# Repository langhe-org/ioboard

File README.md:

# ioboard

This circuit board is the interface between a Beaglebone Black and the rest of the greenhouse components.

## Ordering

The part numbers in the BOM and CPL included in the release are generated for JLC PCB. Alternative part numbers will have to be used for other fabrication houses.

## Assembly BOM

The following components are not included in the PCBA and must be purchased and soldered on separately:

- 1x CUI PDQE20-Q24-S5-D
- 2x Mornsun BO505S-1RW3
- 8x Phoenix Contact 1945119
- 4x Phoenix Contact 1945122

## Mating Connectors

Part numbers to mate the the headers:

- 8x Phoenix Contact 1984031
- 4x Phoenix Contact 1984345

## Enclosure

This board is designed to be housed in a Polycase WH-16 enclosure.

https://www.polycase.com/wh-16

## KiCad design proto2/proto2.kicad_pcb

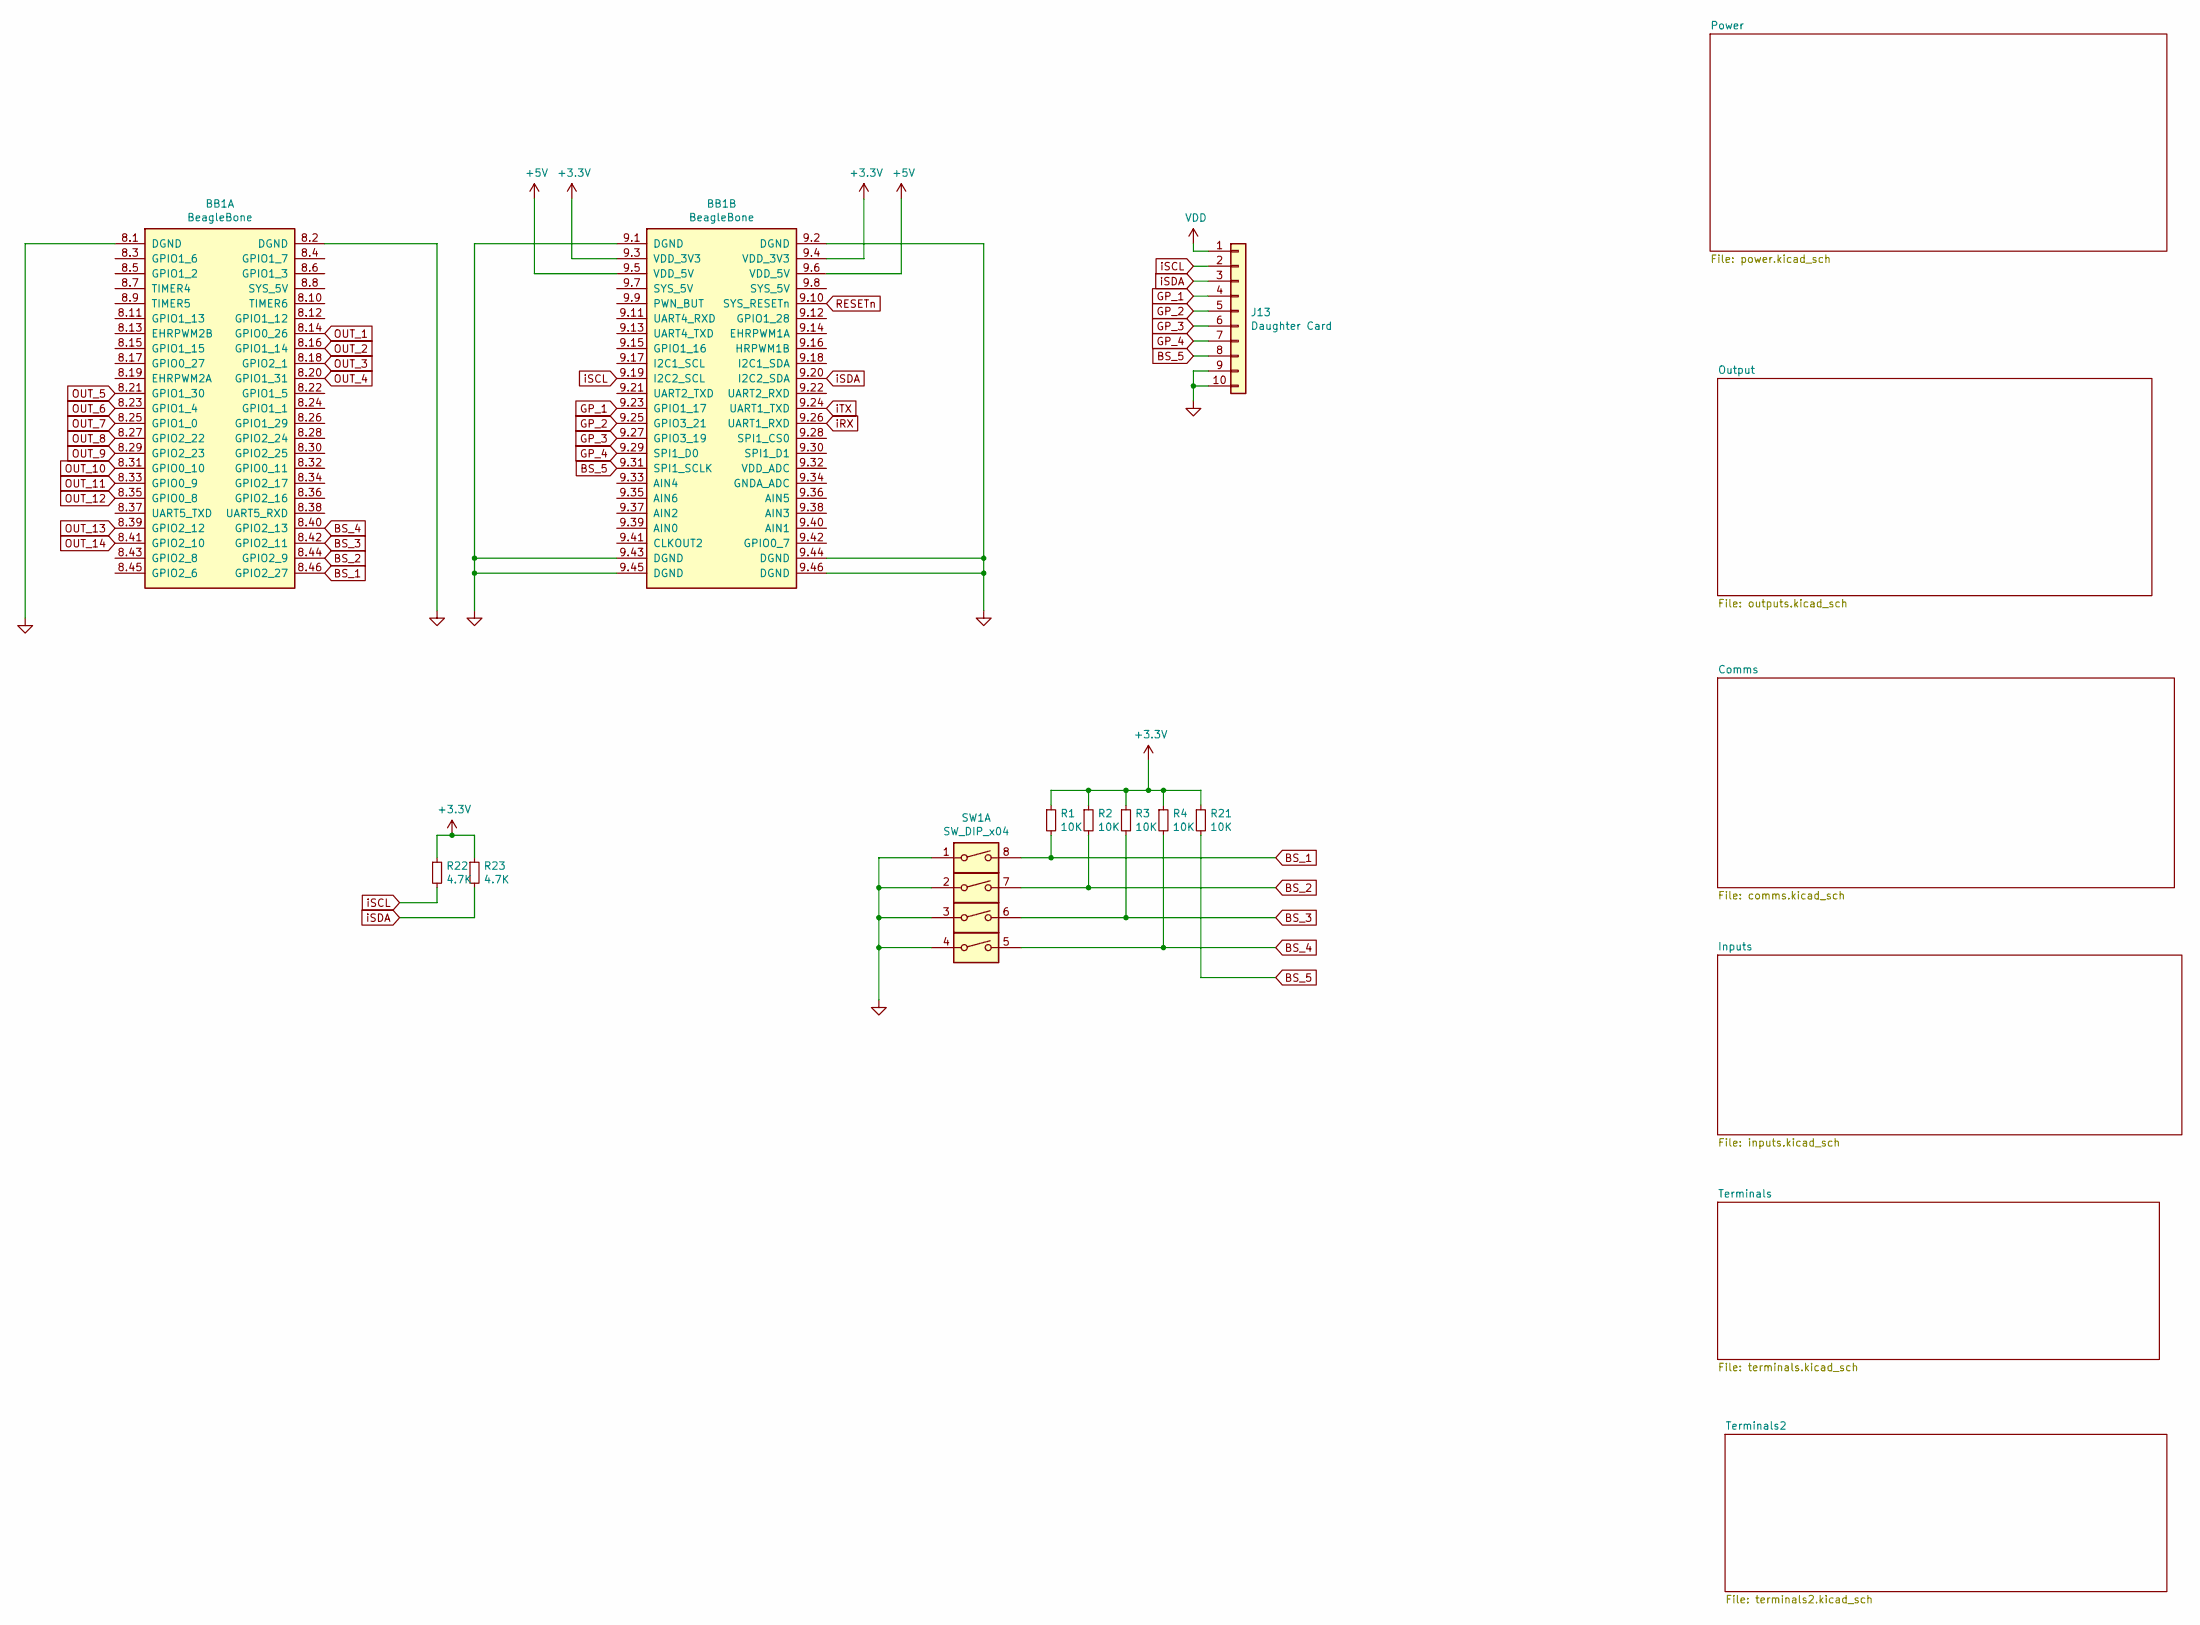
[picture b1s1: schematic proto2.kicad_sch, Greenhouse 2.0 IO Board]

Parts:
BB1: BeagleBone; BeagleBone_UpsideDown
J13: Daughter Card; Proto2_DaughterCard
R1, R2, R3, R4, R21: 10K; R_0805_2012Metric; LCSC C17414
R22, R23: 4.7K; R_0805_2012Metric; LCSC C17673
SW1: SW_DIP_x04; CUI_DS04-254-2-04BK-SMT; Part Number A6S-4101-H; LCSC C306873

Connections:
+5V: BB1.9.5 (VDD_5V), BB1.9.6 (VDD_5V); also elsewhere on the board
BS_1: BB1.8.46 (GPIO2_27), R1.2, SW1.8
BS_2: BB1.8.44 (GPIO2_9), R2.2, SW1.7
BS_3: BB1.8.42 (GPIO2_11), R3.2, SW1.6
BS_4: BB1.8.40 (GPIO2_13), R4.2, SW1.5
BS_5: BB1.9.31 (SPI1_SCLK), J13.8, R21.2
GND-SIG: BB1.8.1 (DGND), BB1.8.2 (DGND), BB1.9.1 (DGND), BB1.9.2 (DGND), BB1.9.43 (DGND), BB1.9.44 (DGND), BB1.9.45 (DGND), BB1.9.46 (DGND), J13.9, J13.10, SW1.1, SW1.2, SW1.3, SW1.4; also elsewhere on the board
GP_1: BB1.9.23 (GPIO1_17), J13.4
GP_2: BB1.9.25 (GPIO3_21), J13.5
GP_3: BB1.9.27 (GPIO3_19), J13.6
GP_4: BB1.9.29 (SPI1_D0), J13.7
OUT_1: BB1.8.14 (GPIO0_26); also elsewhere on the board
OUT_2: BB1.8.16 (GPIO1_14); also elsewhere on the board
OUT_3: BB1.8.18 (GPIO2_1); also elsewhere on the board
OUT_4: BB1.8.20 (GPIO1_31); also elsewhere on the board
OUT_5: BB1.8.21 (GPIO1_30); also elsewhere on the board
OUT_6: BB1.8.23 (GPIO1_4); also elsewhere on the board
OUT_7: BB1.8.25 (GPIO1_0); also elsewhere on the board
OUT_8: BB1.8.27 (GPIO2_22); also elsewhere on the board
OUT_9: BB1.8.29 (GPIO2_23); also elsewhere on the board
OUT_10: BB1.8.31 (GPIO0_10); also elsewhere on the board
OUT_11: BB1.8.33 (GPIO0_9); also elsewhere on the board
OUT_12: BB1.8.35 (GPIO0_8); also elsewhere on the board
OUT_13: BB1.8.39 (GPIO2_12); also elsewhere on the board
OUT_14: BB1.8.41 (GPIO2_10); also elsewhere on the board
RESETn: BB1.9.10 (SYS_RESETn); also elsewhere on the board
VDD: J13.1; also elsewhere on the board
iRX: BB1.9.26 (UART1_RXD); also elsewhere on the board
iSCL: BB1.9.19 (I2C2_SCL), J13.2, R22.2; also elsewhere on the board
iSDA: BB1.9.20 (I2C2_SDA), J13.3, R23.2; also elsewhere on the board
iTX: BB1.9.24 (UART1_TXD); also elsewhere on the board

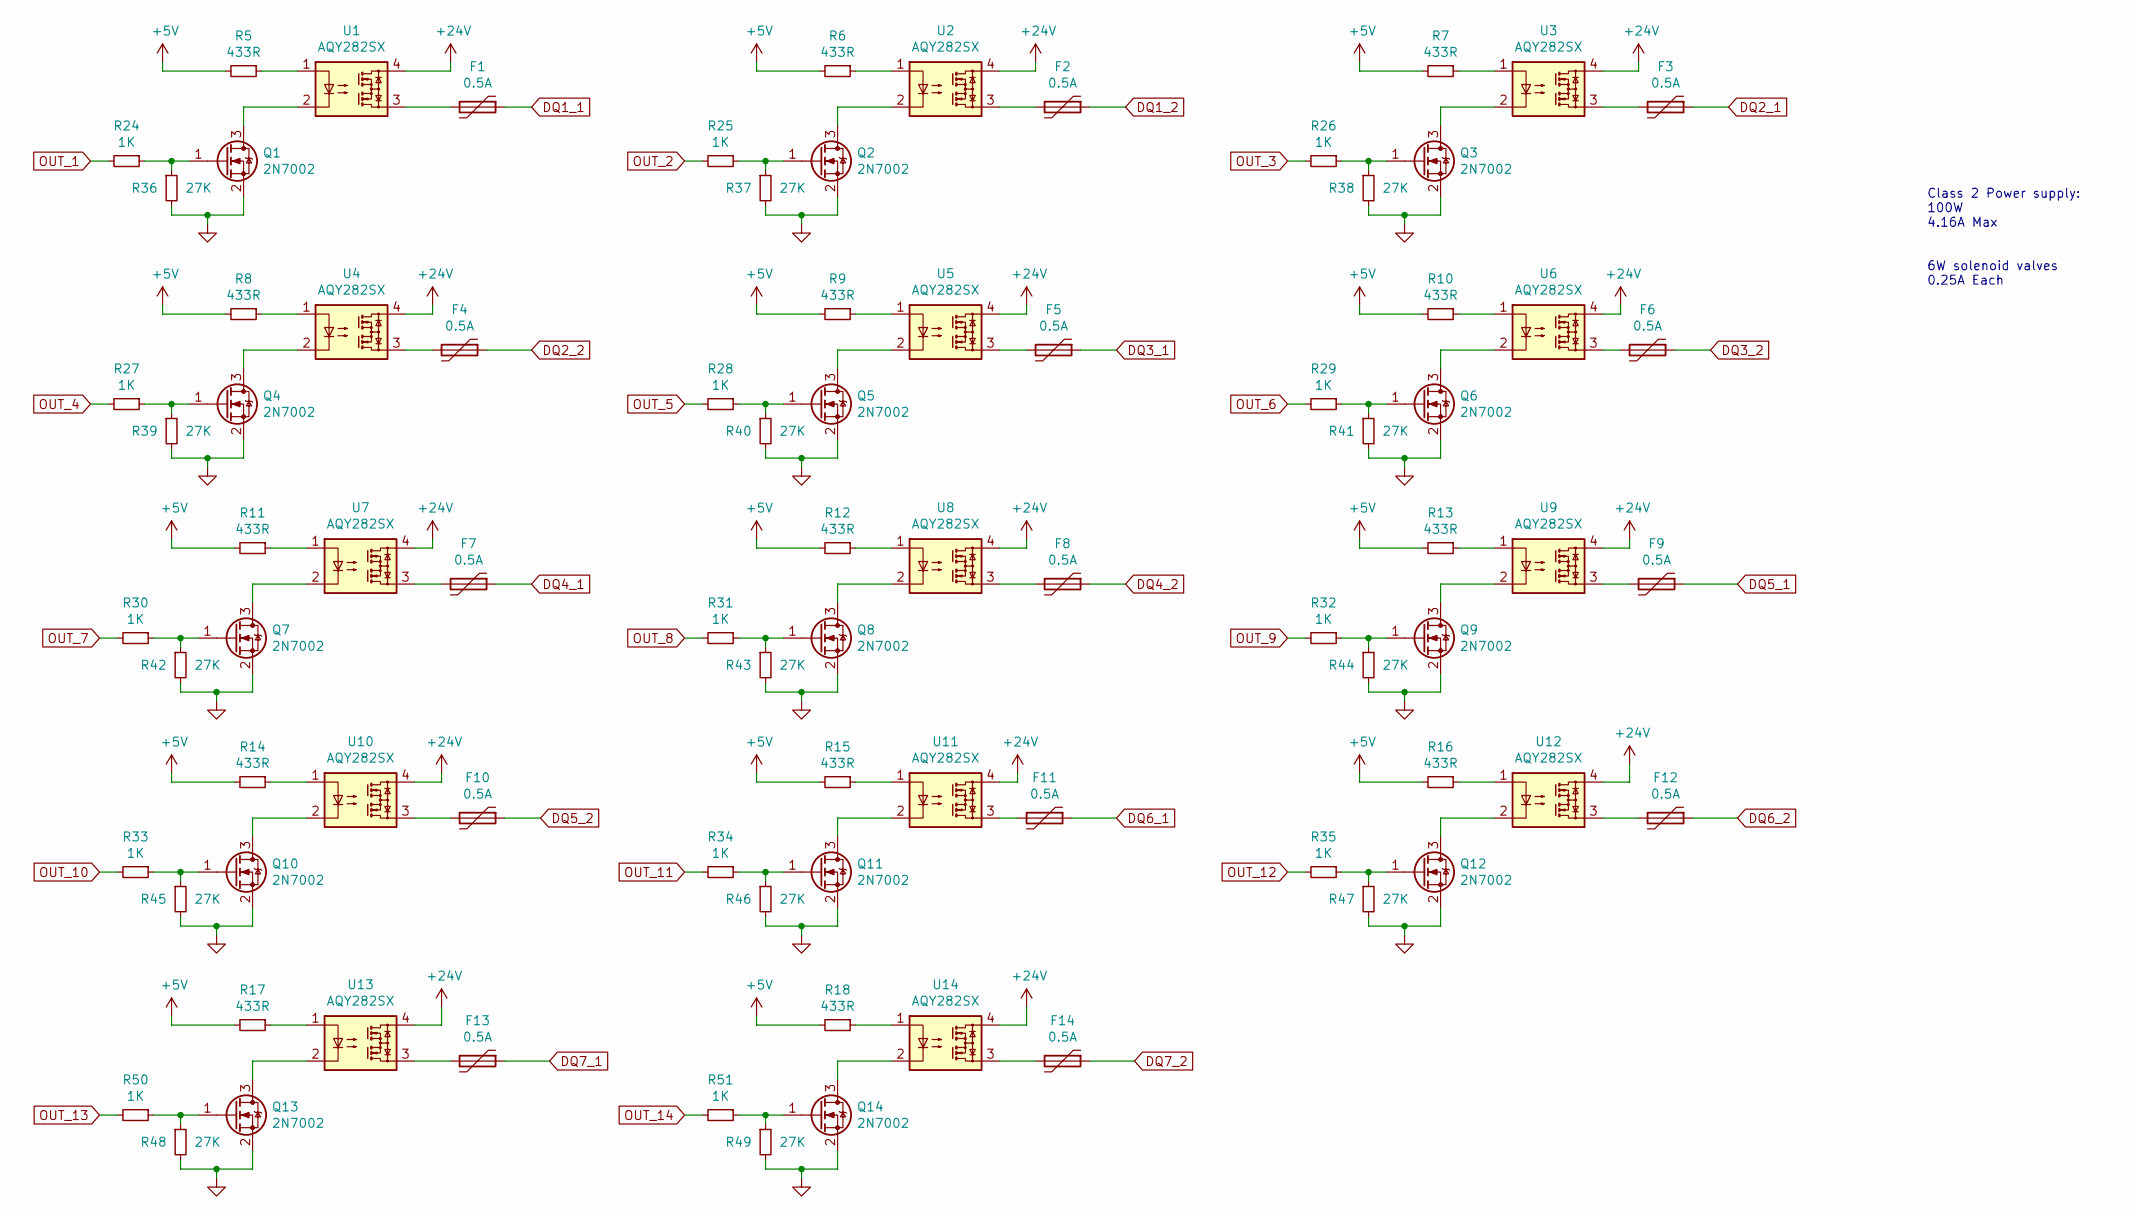
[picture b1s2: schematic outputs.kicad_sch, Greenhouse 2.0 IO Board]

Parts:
F1, F2, F3, F4, F5, F6, F7, F8, F9, F10, F11, F12, F13, F14: 0.5A; R_1206_3216Metric; LCSC C70070
Q1, Q2, Q3, Q4, Q5, Q6, Q7, Q8, Q9, Q10, Q11, Q12, Q13, Q14: 2N7002; SOT-23; LCSC C8545
R5, R6, R7, R8, R9, R10, R11, R12, R13, R14, R15, R16, R17, R18: 433R; R_0805_2012Metric; LCSC C17694
R24, R25, R26, R27, R28, R29, R30, R31, R32, R33, R34, R35, R50, R51: 1K; R_0805_2012Metric; LCSC C17513
R36, R37, R38, R39, R40, R41, R42, R43, R44, R45, R46, R47, R48, R49: 27K; R_0805_2012Metric; LCSC C17593
U1, U2, U3, U4, U5, U6, U7, U8, U9, U10, U11, U12, U13, U14: AQY282SX; SO-4_4.4x4.3mm_P2.54mm; LCSC C250827

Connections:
+5V: R5.2, R6.2, R7.2, R8.2, R9.2, R10.2, R11.2, R12.2, R13.2, R14.2, R15.2, R16.2, R17.2, R18.2; also elsewhere on the board
+24V: U1.4, U2.4, U3.4, U4.4, U5.4, U6.4, U7.4, U8.4, U9.4, U10.4, U11.4, U12.4, U13.4, U14.4; also elsewhere on the board
DQ1_1: F1.1; also elsewhere on the board
DQ1_2: F2.1; also elsewhere on the board
DQ2_1: F3.1; also elsewhere on the board
DQ2_2: F4.1; also elsewhere on the board
DQ3_1: F5.1; also elsewhere on the board
DQ3_2: F6.1; also elsewhere on the board
DQ4_1: F7.1; also elsewhere on the board
DQ4_2: F8.1; also elsewhere on the board
DQ5_1: F9.1; also elsewhere on the board
DQ5_2: F10.1; also elsewhere on the board
DQ6_1: F11.1; also elsewhere on the board
DQ6_2: F12.1; also elsewhere on the board
DQ7_1: F13.1; also elsewhere on the board
DQ7_2: F14.1; also elsewhere on the board
GND-SIG: Q1.2 (S), Q2.2 (S), Q3.2 (S), Q4.2 (S), Q5.2 (S), Q6.2 (S), Q7.2 (S), Q8.2 (S), Q9.2 (S), Q10.2 (S), Q11.2 (S), Q12.2 (S), Q13.2 (S), Q14.2 (S), R36.2, R37.2, R38.2, R39.2, R40.2, R41.2, R42.2, R43.2, R44.2, R45.2, R46.2, R47.2, R48.2, R49.2; also elsewhere on the board
unnamed: F1.2, U1.3
unnamed: F2.2, U2.3
unnamed: F3.2, U3.3
unnamed: F4.2, U4.3
unnamed: F5.2, U5.3
unnamed: F6.2, U6.3
unnamed: F7.2, U7.3
unnamed: F8.2, U8.3
unnamed: F9.2, U9.3
unnamed: F10.2, U10.3
unnamed: F11.2, U11.3
unnamed: F12.2, U12.3
unnamed: F13.2, U13.3
unnamed: F14.2, U14.3
unnamed: Q1.1 (G), R24.1, R36.1
unnamed: Q1.3 (D), U1.2
unnamed: Q2.1 (G), R25.1, R37.1
unnamed: Q2.3 (D), U2.2
unnamed: Q3.1 (G), R26.1, R38.1
unnamed: Q3.3 (D), U3.2
unnamed: Q4.1 (G), R27.1, R39.1
unnamed: Q4.3 (D), U4.2
unnamed: Q5.1 (G), R28.1, R40.1
unnamed: Q5.3 (D), U5.2
unnamed: Q6.1 (G), R29.1, R41.1
unnamed: Q6.3 (D), U6.2
unnamed: Q7.1 (G), R30.1, R42.1
unnamed: Q7.3 (D), U7.2
unnamed: Q8.1 (G), R31.1, R43.1
unnamed: Q8.3 (D), U8.2
unnamed: Q9.1 (G), R32.1, R44.1
unnamed: Q9.3 (D), U9.2
unnamed: Q10.1 (G), R33.1, R45.1
unnamed: Q10.3 (D), U10.2
unnamed: Q11.1 (G), R34.1, R46.1
unnamed: Q11.3 (D), U11.2
unnamed: Q12.1 (G), R35.1, R47.1
unnamed: Q12.3 (D), U12.2
unnamed: Q13.1 (G), R48.1, R50.1
unnamed: Q13.3 (D), U13.2
unnamed: Q14.1 (G), R49.1, R51.1
unnamed: Q14.3 (D), U14.2
unnamed: R5.1, U1.1
unnamed: R6.1, U2.1
unnamed: R7.1, U3.1
unnamed: R8.1, U4.1
unnamed: R9.1, U5.1
unnamed: R10.1, U6.1
unnamed: R11.1, U7.1
unnamed: R12.1, U8.1
unnamed: R13.1, U9.1
unnamed: R14.1, U10.1
unnamed: R15.1, U11.1
unnamed: R16.1, U12.1
unnamed: R17.1, U13.1
unnamed: R18.1, U14.1
OUT_1: R24.2; also elsewhere on the board
OUT_2: R25.2; also elsewhere on the board
OUT_3: R26.2; also elsewhere on the board
OUT_4: R27.2; also elsewhere on the board
OUT_5: R28.2; also elsewhere on the board
OUT_6: R29.2; also elsewhere on the board
OUT_7: R30.2; also elsewhere on the board
OUT_8: R31.2; also elsewhere on the board
OUT_9: R32.2; also elsewhere on the board
OUT_10: R33.2; also elsewhere on the board
OUT_11: R34.2; also elsewhere on the board
OUT_12: R35.2; also elsewhere on the board
OUT_13: R50.2; also elsewhere on the board
OUT_14: R51.2; also elsewhere on the board

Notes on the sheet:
Class 2 Power supply: 100W 4.16A Max 6W solenoid valves 0.25A Each

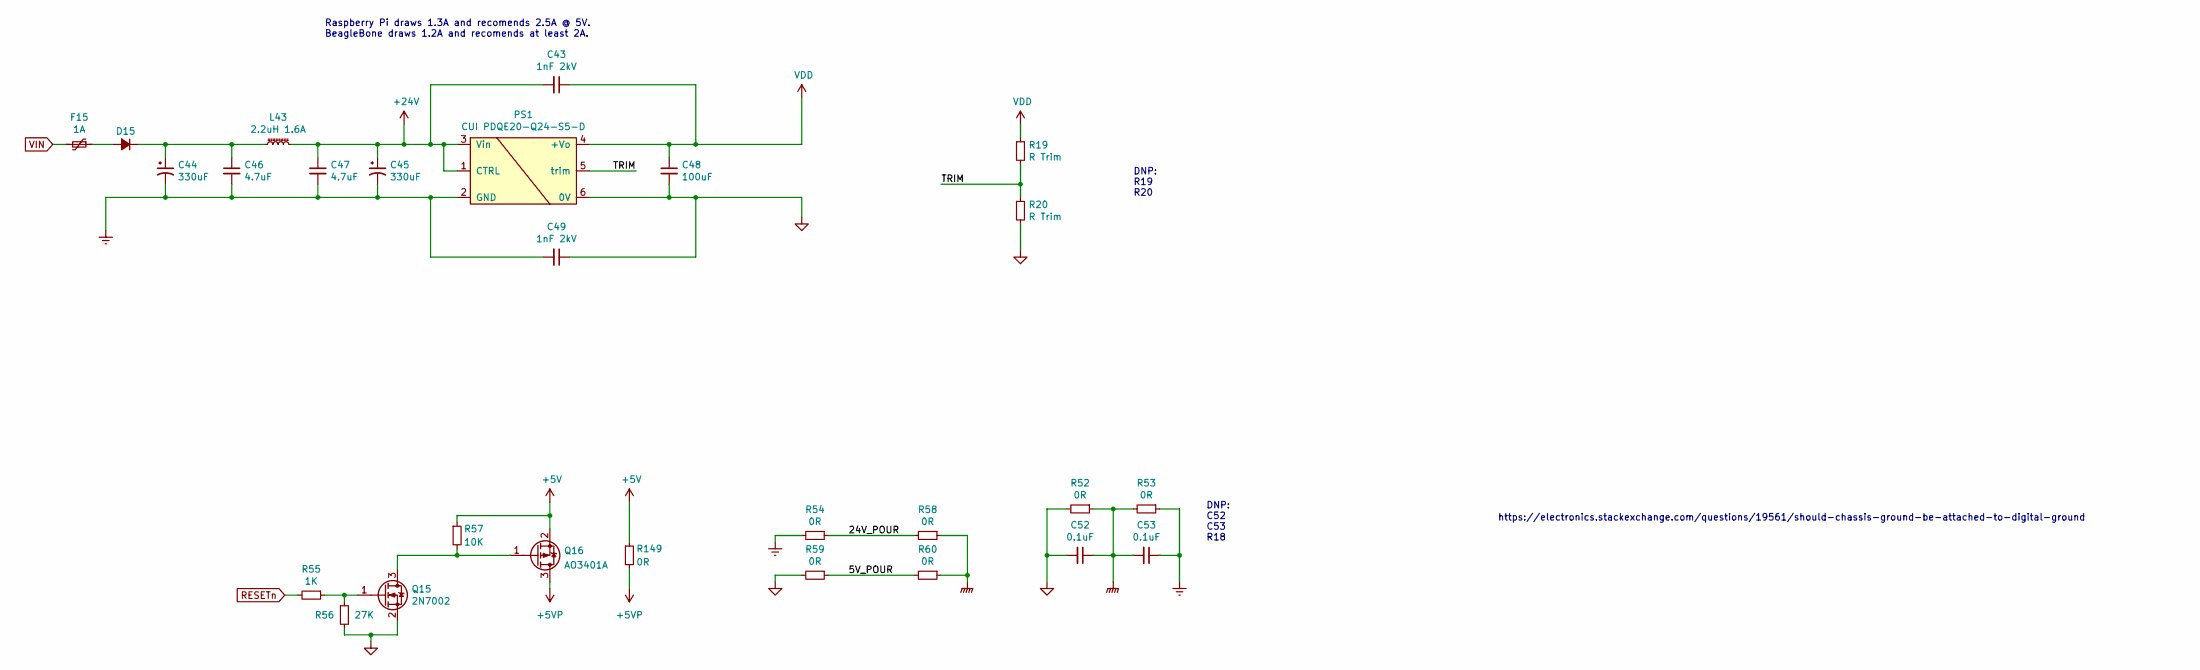
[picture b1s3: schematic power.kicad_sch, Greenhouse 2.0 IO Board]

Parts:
C43, C49: 1nF 2kV; C_1206_3216Metric; LCSC C9196
C44, C45: 330uF; CP_Elec_13x12.5; LCSC C94443
C46, C47: 4.7uF; C_1206_3216Metric; LCSC C29823
C48: 100uF; C_1206_3216Metric; LCSC C312983
C52, C53: 0.1uF; C_0805_2012Metric
D15: D_Small_ALT; D_SOD-123F; Part Number SM4007PL; LCSC C64898
F15: 1A; R_1206_3216Metric; LCSC C70077
L43: 2.2uH 1.6A; Murata_LQH32PN2R2NN0L; Part Number LQH32PN2R2NN0L; LCSC C86074
PS1: CUI PDQE20-Q24-S5-D; CUI_PDQE20; Part Number PDQE20-Q24-S5-D
Q15: 2N7002; SOT-23; LCSC C8545
Q16: AO3401A; SOT-23; Part Number A03401A; LCSC C15127
R19, R20: R Trim; C_0805_2012Metric
R52, R53, R54, R58, R59, R60, R149: 0R; R_0805_2012Metric; LCSC C17477
R55: 1K; R_0805_2012Metric; LCSC C17513
R56: 27K; R_0805_2012Metric; LCSC C17593
R57: 10K; R_0805_2012Metric; LCSC C17414

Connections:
+5V: Q16.2 (S), R57.1, R149.1; also elsewhere on the board
+5VP: Q16.3 (D), R149.2; also elsewhere on the board
+24V: C43.2, C45.1, C47.1, L43.2, PS1.1 (CTRL), PS1.3 (Vin); also elsewhere on the board
/Power/5V_POUR: R59.1, R60.2
/Power/24V_POUR: R54.1, R58.2
/Power/TRIM: PS1.5 (trim), R19.2, R20.1
GND-PE: C52.1, C53.2, R52.1, R53.2, R58.1, R60.1; also elsewhere on the board
GND-PWR: C44.2, C45.2, C46.2, C47.2, C49.2, C53.1, PS1.2 (GND), R53.1, R54.2; also elsewhere on the board
GND-SIG: C48.2, C49.1, C52.2, PS1.6 (0V), Q15.2 (S), R20.2, R52.2, R56.2, R59.2; also elsewhere on the board
unnamed: C44.1, C46.1, D15.1 (K), L43.1
unnamed: D15.2 (A), F15.1
unnamed: Q15.1 (G), R55.1, R56.1
unnamed: Q15.3 (D), Q16.1 (G), R57.2
RESETn: R55.2; also elsewhere on the board
VDD: C43.1, C48.1, PS1.4 (+Vo), R19.1; also elsewhere on the board
VIN: F15.2; also elsewhere on the board

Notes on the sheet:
https://electronics.stackexchange.com/questions/19561/should-chassis-ground-be-attached-to-digital-ground
DNP: R19 R20
Raspberry Pi draws 1.3A and recomends 2.5A @ 5V. BeagleBone draws 1.2A and recomends at least 2A.
DNP: C52 C53 R18

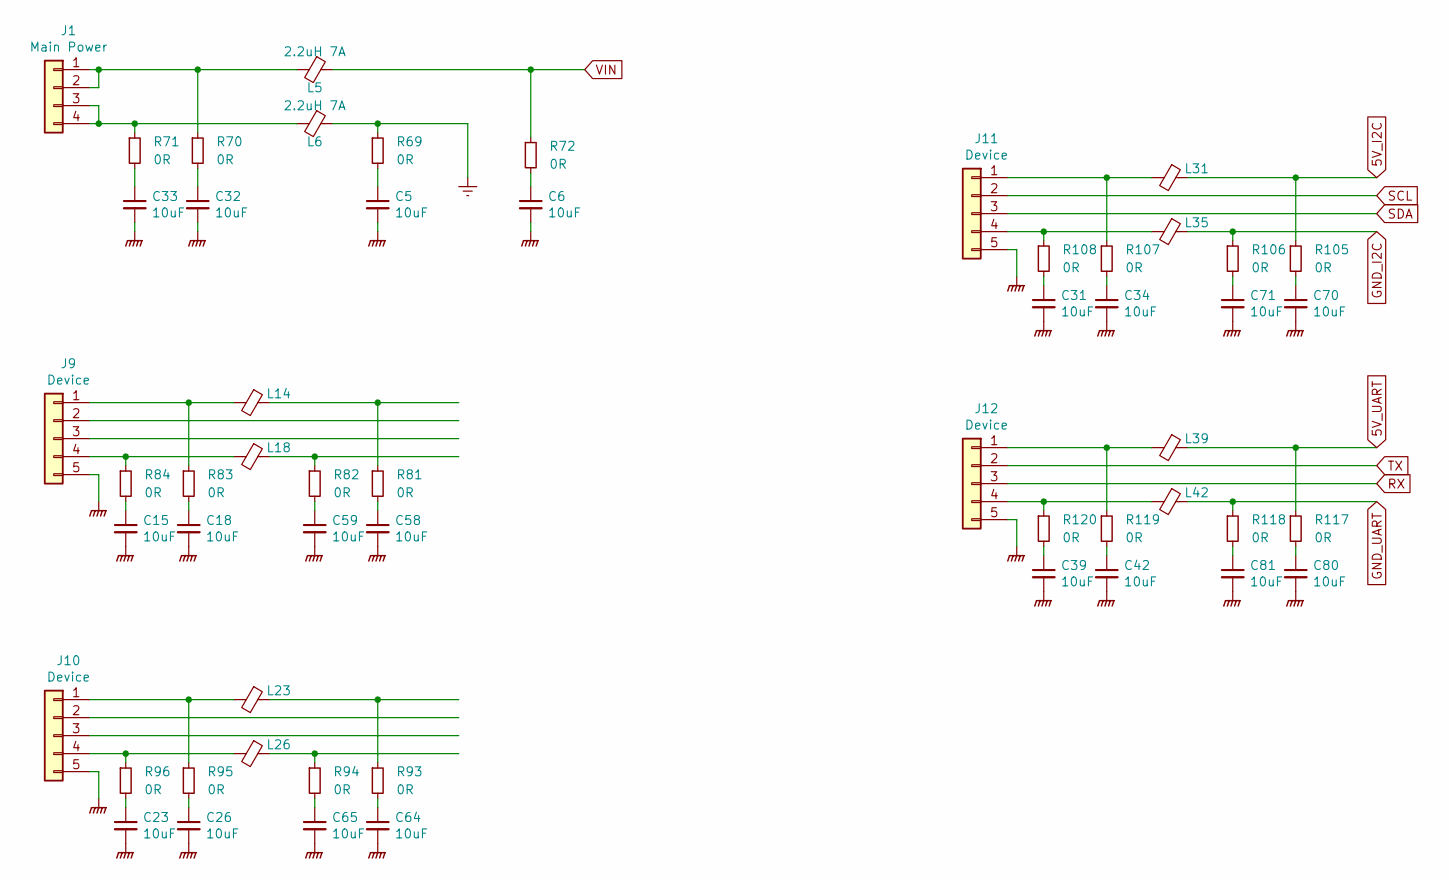
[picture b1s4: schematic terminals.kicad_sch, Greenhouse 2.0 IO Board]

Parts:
C5, C6, C15, C18, C23, C26, C31, C32, C33, C34, C39, C42, C58, C59, C64, C65, C70, C71, C80, C81: 10uF; C_0805_2012Metric; LCSC C440198
J1: Main Power; Phoenix_Contact_PST_4
J9, J10, J11, J12: Device; Phoenix_Contact_PST_5
L5, L6: 2.2uH 7A; Coilmax_MS0630-2R2M; Part Number MS0630-2R2M; LCSC C380175
L14, L18, L23, L26, L31, L35, L39, L42: 10uH 500mA; L_0805_2012Metric; Part Number MGFL2012F100MT; LCSC C281113
R69, R70, R71, R72, R81, R82, R83, R84, R93, R94, R95, R96, R105, R106, R107, R108, R117, R118, R119, R120: 0R; R_0805_2012Metric; LCSC C17477

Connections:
5V_I2C: L31.1, R105.1; also elsewhere on the board
5V_UART: L39.1, R117.1; also elsewhere on the board
GND-PE: C5.2, C6.2, C15.2, C18.2, C23.2, C26.2, C31.2, C32.2, C33.2, C34.2, C39.2, C42.2, C58.2, C59.2, C64.2, C65.2, C70.2, C71.2, C80.2, C81.2, J9.5, J10.5, J11.5, J12.5; also elsewhere on the board
GND-PWR: L6.1, R69.1; also elsewhere on the board
GND_I2C: L35.1, R106.1; also elsewhere on the board
GND_UART: L42.1, R118.1; also elsewhere on the board
unnamed: C5.1, R69.2
unnamed: C6.1, R72.2
unnamed: C15.1, R84.2
unnamed: C18.1, R83.2
unnamed: C23.1, R96.2
unnamed: C26.1, R95.2
unnamed: C31.1, R108.2
unnamed: C32.1, R70.2
unnamed: C33.1, R71.2
unnamed: C34.1, R107.2
unnamed: C39.1, R120.2
unnamed: C42.1, R119.2
unnamed: C58.1, R81.2
unnamed: C59.1, R82.2
unnamed: C64.1, R93.2
unnamed: C65.1, R94.2
unnamed: C70.1, R105.2
unnamed: C71.1, R106.2
unnamed: C80.1, R117.2
unnamed: C81.1, R118.2
unnamed: J1.1, J1.2, L5.2, R70.1
unnamed: J1.3, J1.4, L6.2, R71.1
unnamed: J9.1, L14.2, R83.1
unnamed: J9.4, L18.2, R84.1
unnamed: J10.1, L23.2, R95.1
unnamed: J10.4, L26.2, R96.1
unnamed: J11.1, L31.2, R107.1
unnamed: J11.4, L35.2, R108.1
unnamed: J12.1, L39.2, R119.1
unnamed: J12.4, L42.2, R120.1
unnamed: L14.1, R81.1
unnamed: L18.1, R82.1
unnamed: L23.1, R93.1
unnamed: L26.1, R94.1
RX: J12.3; also elsewhere on the board
SCL: J11.2; also elsewhere on the board
SDA: J11.3; also elsewhere on the board
TX: J12.2; also elsewhere on the board
VIN: L5.1, R72.1; also elsewhere on the board

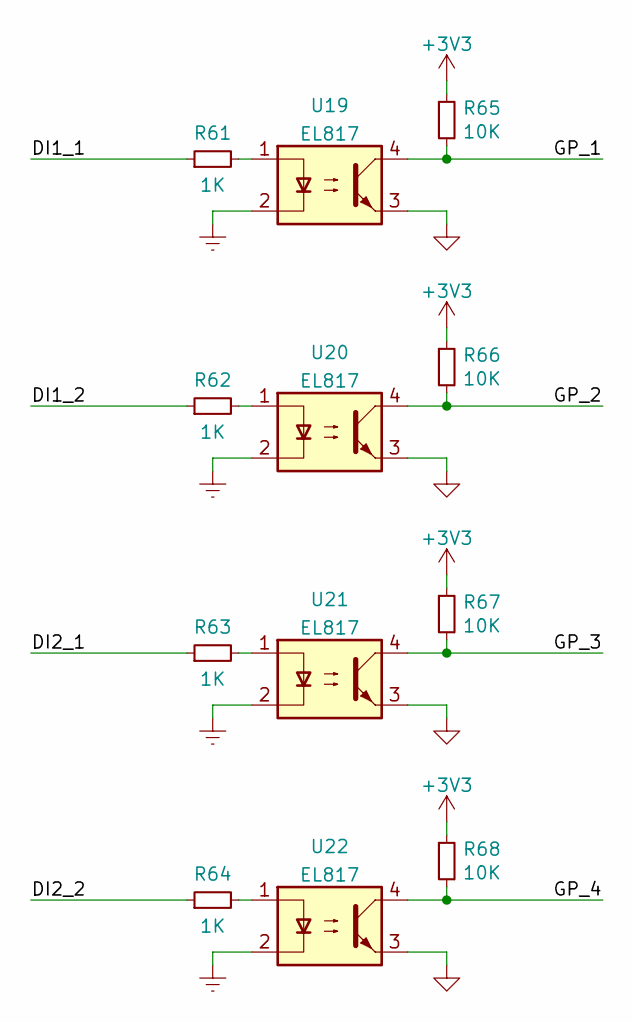
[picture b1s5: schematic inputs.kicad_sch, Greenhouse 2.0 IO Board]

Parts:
R61, R62, R63, R64: 1K; R_0805_2012Metric; LCSC C17513
R65, R66, R67, R68: 10K; R_0805_2012Metric; LCSC C17414
U19, U20, U21, U22: EL817; SO-4_7.6x3.6mm_P2.54mm; Part Number EL817; LCSC C106900

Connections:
/Inputs/DI1_1: R61.1
/Inputs/DI1_2: R62.1
/Inputs/DI2_1: R63.1
/Inputs/DI2_2: R64.1
/Inputs/GP_1: R65.2, U19.4
/Inputs/GP_2: R66.2, U20.4
/Inputs/GP_3: R67.2, U21.4
/Inputs/GP_4: R68.2, U22.4
GND-PWR: U19.2, U20.2, U21.2, U22.2; also elsewhere on the board
GND-SIG: U19.3, U20.3, U21.3, U22.3; also elsewhere on the board
unnamed: R61.2, U19.1
unnamed: R62.2, U20.1
unnamed: R63.2, U21.1
unnamed: R64.2, U22.1

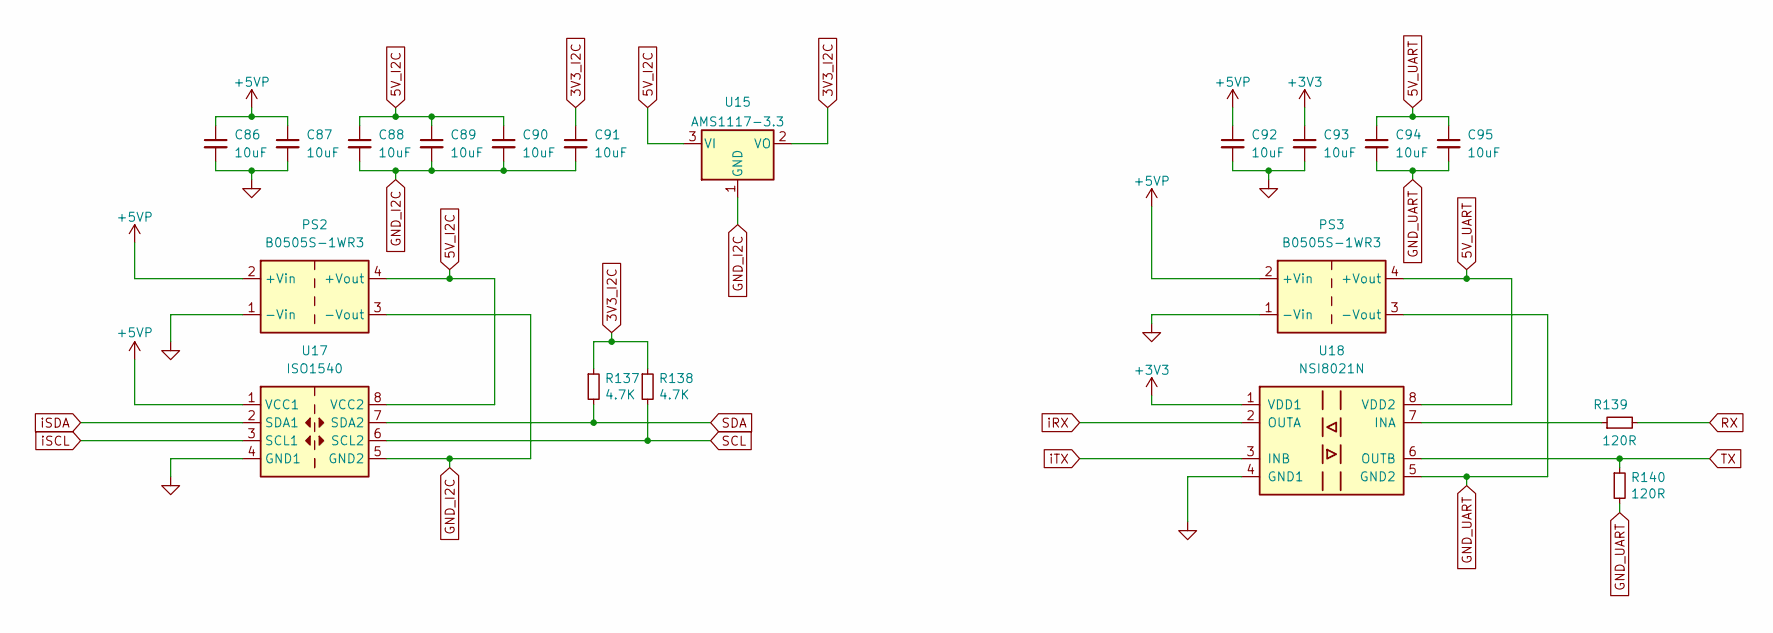
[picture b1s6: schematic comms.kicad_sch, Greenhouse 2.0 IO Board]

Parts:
C86, C87, C88, C89, C90, C91, C92, C93, C94, C95: 10uF; C_0805_2012Metric; LCSC C440198
PS2, PS3: B0505S-1WR3; Converter_DCDC_Murata_MEE1SxxxxSC_THT; LCSC C131038
R137, R138: 4.7K; R_0805_2012Metric; LCSC C17673
R139, R140: 120R; R_0805_2012Metric; LCSC C17437
U15: AMS1117-3.3; SOT-223-3_TabPin2; Part Number AMS1117-3.3; LCSC C6186
U17: ISO1540; SOIC-8_3.9x4.9mm_P1.27mm; Part Number ISO1540DR; LCSC C179739
U18: NSI8021N; SOIC-8_3.9x4.9mm_P1.27mm; Part Number NSI8021N-DSPR; LCSC C917451

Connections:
3V3_I2C: C91.1, R137.1, R138.1, U15.2 (VO)
5V_I2C: C88.1, C89.1, C90.1, PS2.4 (+Vout), U15.3 (VI), U17.8 (VCC2); also elsewhere on the board
5V_UART: C94.1, C95.1, PS3.4 (+Vout), U18.8 (VDD2); also elsewhere on the board
+5VP: C86.1, C87.1, C92.1, PS2.2 (+Vin), PS3.2 (+Vin), U17.1 (VCC1); also elsewhere on the board
GND-SIG: C86.2, C87.2, C92.2, C93.2, PS2.1 (-Vin), PS3.1 (-Vin), U17.4 (GND1), U18.4 (GND1); also elsewhere on the board
GND_I2C: C88.2, C89.2, C90.2, C91.2, PS2.3 (-Vout), U15.1 (GND), U17.5 (GND2); also elsewhere on the board
GND_UART: C94.2, C95.2, PS3.3 (-Vout), R140.2, U18.5 (GND2); also elsewhere on the board
unnamed: R139.1, U18.7 (INA)
RX: R139.2; also elsewhere on the board
SCL: R138.2, U17.6 (SCL2); also elsewhere on the board
SDA: R137.2, U17.7 (SDA2); also elsewhere on the board
TX: R140.1, U18.6 (OUTB); also elsewhere on the board
iRX: U18.2 (OUTA); also elsewhere on the board
iSCL: U17.3 (SCL1); also elsewhere on the board
iSDA: U17.2 (SDA1); also elsewhere on the board
iTX: U18.3 (INB); also elsewhere on the board

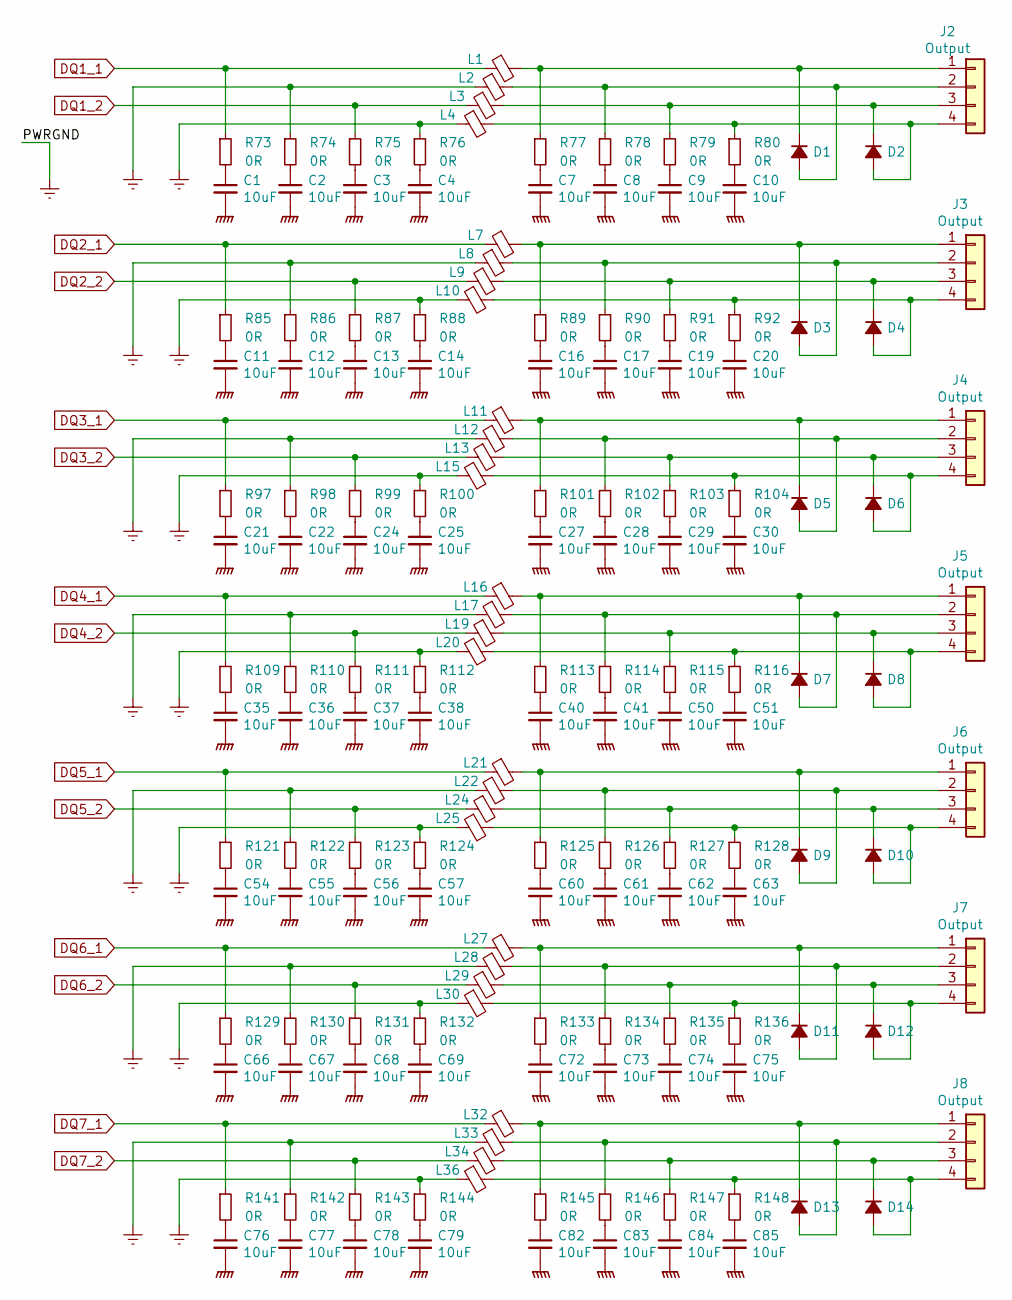
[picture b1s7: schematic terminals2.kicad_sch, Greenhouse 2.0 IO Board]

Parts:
C1, C2, C3, C4, C7, C8, C9, C10, C11, C12, C13, C14, C16, C17, C19, C20, C21, C22, C24, C25, C27, C28, C29, C30, C35, C36, C37, C38, C40, C41, C50, C51, C54, C55, C56, C57, C60, C61, C62, C63, C66, C67, C68, C69, C72, C73, C74, C75, C76, C77, C78, C79, C82, C83, C84, C85: 10uF; C_0805_2012Metric; LCSC C440198
D1, D2, D3, D4, D5, D6, D7, D8, D9, D10, D11, D12, D13, D14: D_Small_ALT; D_SOD-123F; Part Number SM4007PL; LCSC C64898
J2, J3, J4, J5, J6, J7, J8: Output; Phoenix_Contact_PST_4
L1, L2, L3, L4, L7, L8, L9, L10, L11, L12, L13, L15, L16, L17, L19, L20, L21, L22, L24, L25, L27, L28, L29, L30, L32, L33, L34, L36: 10uH 500mA; L_0805_2012Metric; Part Number MGFL2012F100MT; LCSC C281113
R73, R74, R75, R76, R77, R78, R79, R80, R85, R86, R87, R88, R89, R90, R91, R92, R97, R98, R99, R100, R101, R102, R103, R104, R109, R110, R111, R112, R113, R114, R115, R116, R121, R122, R123, R124, R125, R126, R127, R128, R129, R130, R131, R132, R133, R134, R135, R136, R141, R142, R143, R144, R145, R146, R147, R148: 0R; R_0805_2012Metric; LCSC C17477

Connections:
DQ1_1: L1.1, R73.1; also elsewhere on the board
DQ1_2: L3.1, R75.1; also elsewhere on the board
DQ2_1: L7.1, R85.1; also elsewhere on the board
DQ2_2: L9.1, R87.1; also elsewhere on the board
DQ3_1: L11.1, R97.1; also elsewhere on the board
DQ3_2: L13.1, R99.1; also elsewhere on the board
DQ4_1: L16.1, R109.1; also elsewhere on the board
DQ4_2: L19.1, R111.1; also elsewhere on the board
DQ5_1: L21.1, R121.1; also elsewhere on the board
DQ5_2: L24.1, R123.1; also elsewhere on the board
DQ6_1: L27.1, R129.1; also elsewhere on the board
DQ6_2: L29.1, R131.1; also elsewhere on the board
DQ7_1: L32.1, R141.1; also elsewhere on the board
DQ7_2: L34.1, R143.1; also elsewhere on the board
GND-PE: C1.2, C2.2, C3.2, C4.2, C7.2, C8.2, C9.2, C10.2, C11.2, C12.2, C13.2, C14.2, C16.2, C17.2, C19.2, C20.2, C21.2, C22.2, C24.2, C25.2, C27.2, C28.2, C29.2, C30.2, C35.2, C36.2, C37.2, C38.2, C40.2, C41.2, C50.2, C51.2, C54.2, C55.2, C56.2, C57.2, C60.2, C61.2, C62.2, C63.2, C66.2, C67.2, C68.2, C69.2, C72.2, C73.2, C74.2, C75.2, C76.2, C77.2, C78.2, C79.2, C82.2, C83.2, C84.2, C85.2; also elsewhere on the board
GND-PWR: L2.1, L4.1, L8.1, L10.1, L12.1, L15.1, L17.1, L20.1, L22.1, L25.1, L28.1, L30.1, L33.1, L36.1, R74.1, R76.1, R86.1, R88.1, R98.1, R100.1, R110.1, R112.1, R122.1, R124.1, R130.1, R132.1, R142.1, R144.1; also elsewhere on the board
unnamed: C1.1, R73.2
unnamed: C2.1, R74.2
unnamed: C3.1, R75.2
unnamed: C4.1, R76.2
unnamed: C7.1, R77.2
unnamed: C8.1, R78.2
unnamed: C9.1, R79.2
unnamed: C10.1, R80.2
unnamed: C11.1, R85.2
unnamed: C12.1, R86.2
unnamed: C13.1, R87.2
unnamed: C14.1, R88.2
unnamed: C16.1, R89.2
unnamed: C17.1, R90.2
unnamed: C19.1, R91.2
unnamed: C20.1, R92.2
unnamed: C21.1, R97.2
unnamed: C22.1, R98.2
unnamed: C24.1, R99.2
unnamed: C25.1, R100.2
unnamed: C27.1, R101.2
unnamed: C28.1, R102.2
unnamed: C29.1, R103.2
unnamed: C30.1, R104.2
unnamed: C35.1, R109.2
unnamed: C36.1, R110.2
unnamed: C37.1, R111.2
unnamed: C38.1, R112.2
unnamed: C40.1, R113.2
unnamed: C41.1, R114.2
unnamed: C50.1, R115.2
unnamed: C51.1, R116.2
unnamed: C54.1, R121.2
unnamed: C55.1, R122.2
unnamed: C56.1, R123.2
unnamed: C57.1, R124.2
unnamed: C60.1, R125.2
unnamed: C61.1, R126.2
unnamed: C62.1, R127.2
unnamed: C63.1, R128.2
unnamed: C66.1, R129.2
unnamed: C67.1, R130.2
unnamed: C68.1, R131.2
unnamed: C69.1, R132.2
unnamed: C72.1, R133.2
unnamed: C73.1, R134.2
unnamed: C74.1, R135.2
unnamed: C75.1, R136.2
unnamed: C76.1, R141.2
unnamed: C77.1, R142.2
unnamed: C78.1, R143.2
unnamed: C79.1, R144.2
unnamed: C82.1, R145.2
unnamed: C83.1, R146.2
unnamed: C84.1, R147.2
unnamed: C85.1, R148.2
unnamed: D1.1 (K), J2.1, L1.2, R77.1
unnamed: D1.2 (A), J2.2, L2.2, R78.1
unnamed: D2.1 (K), J2.3, L3.2, R79.1
unnamed: D2.2 (A), J2.4, L4.2, R80.1
unnamed: D3.1 (K), J3.1, L7.2, R89.1
unnamed: D3.2 (A), J3.2, L8.2, R90.1
unnamed: D4.1 (K), J3.3, L9.2, R91.1
unnamed: D4.2 (A), J3.4, L10.2, R92.1
unnamed: D5.1 (K), J4.1, L11.2, R101.1
unnamed: D5.2 (A), J4.2, L12.2, R102.1
unnamed: D6.1 (K), J4.3, L13.2, R103.1
unnamed: D6.2 (A), J4.4, L15.2, R104.1
unnamed: D7.1 (K), J5.1, L16.2, R113.1
unnamed: D7.2 (A), J5.2, L17.2, R114.1
unnamed: D8.1 (K), J5.3, L19.2, R115.1
unnamed: D8.2 (A), J5.4, L20.2, R116.1
unnamed: D9.1 (K), J6.1, L21.2, R125.1
unnamed: D9.2 (A), J6.2, L22.2, R126.1
unnamed: D10.1 (K), J6.3, L24.2, R127.1
unnamed: D10.2 (A), J6.4, L25.2, R128.1
unnamed: D11.1 (K), J7.1, L27.2, R133.1
unnamed: D11.2 (A), J7.2, L28.2, R134.1
unnamed: D12.1 (K), J7.3, L29.2, R135.1
unnamed: D12.2 (A), J7.4, L30.2, R136.1
unnamed: D13.1 (K), J8.1, L32.2, R145.1
unnamed: D13.2 (A), J8.2, L33.2, R146.1
unnamed: D14.1 (K), J8.3, L34.2, R147.1
unnamed: D14.2 (A), J8.4, L36.2, R148.1

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

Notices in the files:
proto2/proto2.kicad_pcb:
LANGHE ©2022
